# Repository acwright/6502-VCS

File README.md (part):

6502-VCS
========

An **AC6502** retro-style 8-bit computer based on the **65C02** microprocessor.

> 📖 **Guide:** [AC6502 Documentation](https://acwright.github.io/6502-DOCS/) — the user's and programmer's guide for the whole family.
> See [VCS's page in the family appendix](https://acwright.github.io/6502-DOCS/family/vcs).

---

**Building one? Every part you need, with supplier numbers and known issues, is in [BOM.md](BOM.md).**

## Table of Contents

- [Overview](#overview)
- [Architecture](#architecture)
- [Systems](#systems)
- [Software](#software)
- [Hardware](#hardware)
  - [Main Board](#main-board)
  - [Input Board](#input-board)
  - [Output Board](#output-board)
  - [ROM Cart](#rom-cart)
  - [Flash Cart](#flash-cart)
  - [Flash Helper](#flash-helper)
- [Which revision to make](#which-revision-to-make)
- [Works with the stock BIOS](#works-with-the-stock-bios)
- [Firmware](#firmware)
  - [IB Controller](#ib-controller)
- [CAD](#cad)
- [Production](#production)
- [Schematics](#schematics)
- [Shared lines](#shared-lines)
- [Extra pins: `EXP0`–`EXP3` and `HRDB`](#extra-pins-exp0exp3-and-hrdb)
- [Jumpers](#jumpers)
- [Off-board headers](#off-board-headers)
- [Libraries](#libraries)
- [Bill of Materials](#bill-of-materials)
- [License](#license)

---

## Overview

The AC6502 ecosystem is a family of open-source, 65C02-based computers sharing a common architecture, memory map, and [BIOS](https://github.com/acwright/6502-BIOS). Each computer in the family is purpose-built for a different use case but runs the same software and firmware.

The **VCS** is a cartridge-based retro gaming console. It features a real 65C02 CPU, swappable ROM cartridges, VGA video output via [Pico9918](https://github.com/visrealm/pico9918), SID audio via ARMSID, and support for PS/2 keyboards, matrix keyboards, and Atari 2600-compatible joysticks.

## Architecture

All AC6502 computers share:

- **CPU**: 65C02 (or accurate emulation)
- **Memory**: 32KB RAM + 32KB ROM, with optional banked RAM expansion
- **Memory Map**: Standardized across the ecosystem — zero page, stack, I/O space ($8000–$9FFF), system ROM, and interrupt vectors at $FFFA–$FFFF
- **Bus**: 16-bit address bus, 8-bit bidirectional data bus, standard 65C02 control signals (RW, PHI2, RESET, IRQ, NMI, RDY, SYNC)
- **BIOS**: A common [BIOS](https://github.com/acwright/6502-BIOS) provides the kernel, monitor, and BASIC interpreter across all systems

## Systems

| Project | Description |
|---------|-------------|
| [6502-ACE](https://github.com/acwright/6502-ACE) | All-in-one Computer Experience — A single board computer |
| [6502-COB](https://github.com/acwright/6502-COB) | Computer On a Backplane — Modular desktop computer with expandable card slots |
| [6502-DEV](https://github.com/acwright/6502-DEV) | Development Environment Vehicle — Emulation-based dev system |
| [6502-KIM](https://github.com/acwright/6502-KIM) | Keypad Input Monitor - KIM-1 inspired minimal computer |
| [6502-VCS](https://github.com/acwright/6502-VCS) | Video Computer System — Cartridge-based retro gaming console (YOU ARE HERE) |

## Software

| Project | Description |
|---------|-------------|
| [6502-BIOS](https://github.com/acwright/6502-BIOS) | The shared BIOS (kernel, monitor, BASIC) for all AC6502 computers |
| [6502-EMULATOR](https://github.com/acwright/6502-EMULATOR) | Emulator for the whole family — desktop app, browser build, and a command line for scripted runs |
| [6502-PRG](https://github.com/acwright/6502-PRG) | Template project for writing assembly language programs |
| [6502-CRT](https://github.com/acwright/6502-CRT) | Template project for writing assembly language cartridges |
| [6502-ASM](https://github.com/acwright/6502-ASM) | Assembly language example programs and demos |
| [6502-BAS](https://github.com/acwright/6502-BAS) | BASIC program listings |
| [6502-WOZMON](https://github.com/acwright/6502-WOZMON) | Wozmon as a standalone ROM |
| [6502-NOP](https://github.com/acwright/6502-NOP) | An all-NOP ROM, for probing a board during bring-up |
| [6502-DOCS](https://github.com/acwright/6502-DOCS) | The documentation site — the guide, the printable reference cards, branding and label artwork |
| [cffs](https://github.com/acwright/cffs) | Builds CompactFlash disk images for the BIOS filesystem |
| [bastok](https://github.com/acwright/bastok) | Tokenizes BASIC listings into `.prg` images, and back |
| [bin2woz](https://github.com/acwright/bin2woz) | Converts a binary into a Wozmon serial upload |

## Hardware

This repository contains KiCad 7.0+ PCB designs for the boards that make up the VCS system.

### Main Board
`Hardware/Main Board/`

The core board containing the 65C02 CPU, 32KB SRAM, 32KB EEPROM, clock, and reset circuitry. Runs at 1 MHz and provides the bus connection for the Input and Output boards.

### Input Board
`Hardware/Input Board/`

Unified input board supporting a matrix keyboard, PS/2 keyboard, and Atari 2600-compatible joysticks. Uses a 65C22 VIA and an ATmega1284 microcontroller as the keyboard encoder controller.

The joysticks share the VIA ports with the keyboard encoder rather than having connectors of their own: they come in on the `J1` PORT B and `J2` PORT A box headers, with `JOY(1)` reading PORT B and `JOY(2)` reading PORT A. See [Joystick Interface](./Firmware/IB%20Controller/README.md#joystick-interface) for the wiring options and the bitmask the BIOS returns.

### Output Board
`Hardware/Output Board/`

Combined VGA video output (via Raspberry Pi Pico running [Pico9918](https://github.com/visrealm/pico9918)) and SID audio output (via ARMSID). Provides TMS9918A-compatible graphics modes at 640×480 VGA and 3-voice SID synthesis.

### ROM Cart
`Hardware/ROM Cart/`

Swappable ROM cartridge for the VCS system. Rev 1.0 came in two versions, one for each ROM chip:

- **Rev 1.0a** — Uses the **28C256** 32KB EEPROM (electrically erasable, no UV eraser required).
- **Rev 1.0b** — Uses the **27C256** 32KB EPROM (UV-erasable).

**Rev 1.1** (drawn, not yet made) takes either chip. Two solder jumpers, JP1 and JP2, ship set for the 28C256
(`28C`); cut and re-bridge both to `27C` for a 27C256. It also has an option for tinkerers, not fitted:
J2, `ROM BANK`, picks the chip's upper 16K (`HI`, as made) or its lower 16K (`LO`), so one chip can hold two
programs. See *Jumpers* below and the build notes in `BOM.md`.

### Flash Cart
`Hardware/Flash Cart/`

Banked flash cartridge, and the successor to the fixed 16K ROM Cart. One all-SMD board covers 128KB to 1MB,
depending on which parts are populated, and the flash is programmed in circuit through the card edge, either by
the Flash Helper (an Arduino Mega 2560 shield with one connector on it) or by the 6502 itself.

- `$C000–$DFFF` is a switchable 8K window, selected by a write-only bank register at `$E000–$FFFF`.
- `$E000–$FFFF` is fixed to the last 8K of the primary flash, so the vectors and the bank-switching code can
  never be mapped out.
- Existing 16K cart images run unmodified.
- **Tested in the 512KB and 1MB builds** (2026-11-09): programmed through the Flash Helper, and run on an ACE,
  banking into both chips and saving across a power cycle. The 128KB and 256KB builds (SST39SF010A, SST39SF020A)
  use the same board but haven't been built yet.
- Its 0.5 mm TSOP parts make it the hardest board in the family to build by hand: having JLCPCB assemble it is the
  preferred way to get one. See the build notes in [BOM.md](BOM.md#build-notes).

See [DESIGN.md](./Hardware/Flash%20Cart/Rev%201.0/DESIGN.md) for the memory map, the logic, the programming
sequences and the build variants.

### Flash Helper
`Hardware/Flash Helper/`

The programmer for the Flash Cart: an Arduino Mega 2560 R3 shield with a cartridge slot on it, and
nothing else. It pretends to be the 65C02 on the far side of the card edge, so a cart is programmed
in circuit with no chip ever removed — which matters, because the flash is a soldered-down TSOP part.

- Two parts: the Arduino, and the same TE card edge connector the Main Board fits as J9.
- Thirty-seven of the forty card edge pins: `A0–A15`, `D0–D7`, `RWB`, `PHI2`, `RESB`, `IRQB`, `NMIB`,
  `VCC` and `GND`.
- `EXP0` and `EXP1` are deliberately **not** connected. Cartridges tie them to GND to disable the
  system ROM, so driving them would be a short.
- Host side is `6502-flash`, a Node CLI. See [DESIGN.md](./Hardware/Flash%20Cart/Rev%201.0/DESIGN.md).

**As a card tester.** Every card in the AC6502 family — the [COB](https://github.com/acwright/6502-COB)
cards, the [KIM](https://github.com/acwright/6502-KIM) Keypad Card and both VCS carts — carries the same
`6502 Card Edge` fingers and drops into this socket. `IRQB` and `NMIB` are wired for that reason rather
than for programming: the GPIO, LCD, Serial and Serial Card Pro cards all assert `IRQB`, and a tester
that could not see it would miss most of what they do. That firmware is a separate build and does not
exist yet.

<!-- Which revision to make: generated by Tools/revision-audit/register.py from Tools/data/orders.json. Edit that file, not this section. -->
## Which revision to make

**Make the newest revision of a board, and check its label first.** The table below gives each board's newest revision. A newer revision fixes what was found on the older ones. Every revision, old and new, is in [REVISIONS.md](REVISIONS.md), with what changed in each.

Each revision carries one of three labels:

- **Tested:** This revision was built and tested.
- **Proven design:** Not built at this revision, but its circuit is proven. Either it is a tested revision's circuit, or each change copies a circuit built and tested on another board or on the bench, or is a textbook circuit that leaves everything the tested revision does as it was. Any other change is silkscreen text, part values, mounting holes, outline clean-up, parts moved a fraction of a millimetre onto their grid, capacitor pitch, socket outlines, a footprint swap with the same holes, a solder jumper's default, the solder mask or paste at a card edge, or tracks rerouted or pours refilled with DRC and the netlist check passing. A builder can treat it as tested.
- **Untested:** The circuit, the power path or the layout changed in a way that only a built board proves, or the board has never been built at all.

[BOM.md](BOM.md) has the parts for every revision, and its known issues.

| Board | Newest revision | Label | Why |
|---|---|---|---|
| Flash Cart | 1.1 | **Proven design** | The bare card edge and the shell's holes at their nominal places. |
| Flash Helper | 1.1 | **Proven design** | J1's reference resized and the logo moved; silkscreen only. |
| Input Board | 1.1 | **Proven design** | Silkscreen text, and 10k pull-ups on the PS/2 lines, a textbook circuit not yet tried on these lines. |
| Main Board | 1.1 | **Proven design** | 10k pull-ups, small part moves and tracks rerouted, a 74HCT00 at U5, and the RAM's output enable from inverted `RWB`, tested on an ACE. The jumpers are gone, and `HRDB` is wired as it is on the tested Rev 1.0 with them fitted. |
| Output Board | 1.1 | **Proven design** | `A1` wired to the pico9918's `MODE1`, so the VCS can run BIOS 2.x, as the tested ACE is wired; a second RCA jack beside J2, on the same signal, as on the ACE; ordinary sockets in place of ZIF, on the ACE's footprints; silkscreen text, the `VDD` header removed, JP1 ships open, and JP2 and JP3 removed and wired as Rev 1.0 ships them. |
| ROM Cart | 1.1 | **Proven design** | Either ROM chip through two solder jumpers, each setting a tested board's wiring; a ROM bank option, not fitted, whose pull-up reads the half Rev 1.0 reads; capacitor pitch; the bare card edge and the shell's holes at their nominal places. |
<!-- End of which revision to make -->

<!-- Stock BIOS: generated by Tools/bios/gen.py from Tools/data/bios.json. Edit that file, not this section. -->
## Works with the stock BIOS

Whether each board works with the stock BIOS, and what it takes if not. The stock BIOS for the VCS is **BIOS 1.x**, from the `v1.x` branch of [6502-BIOS](https://github.com/acwright/6502-BIOS). The ACE runs BIOS 2.x, for a 6502-PICOVDP. A VCS can also run BIOS 2.x with an Output Board 1.1, or an Output Board 1.0 with the optional wire in its build note, carrying a PICO9918 PRO running 6502-PICOVDP, set up as the [ACE's video card](https://github.com/acwright/6502-ACE#video-card) is. Today's VCSs, built with an Output Board 1.0, stay on BIOS 1.x. The BIOS looks for each card in its own 1 KB window at boot, and uses only what it finds.

- **Compatible:** the BIOS finds the board and uses it, built from its parts list with the jumpers the [Jumpers](#jumpers) table gives. A card counts only on the window the BIOS expects; on another window it's the builder's experiment.
- **After a step:** it works once the builder does what the entry names, beyond the parts list and the jumpers.
- **Not used by the BIOS:** safe beside it, but your own software drives it.
- **Nothing to support:** the board has no registers for the BIOS to find, such as a backplane, a helper behind a card, or a cartridge's programmer.

| Board | Rev | Stock BIOS | Why | Source |
|---|---|---|---|---|
| Flash Cart | 1.0, 1.1 | **Compatible** | A cartridge: with one in, `HRDB` gives it `$C000`–`$FFFF` and the reset vector, and its program calls the BIOS's Kernal, which stays at `$A000`–`$B7FF`. | README [Extra pins](#extra-pins-exp0exp3-and-hrdb); bench, 2026-11-09 |
| Flash Helper | 1.0, 1.1 | **Nothing to support** | A programmer for the Flash Cart, on an Arduino Mega: it's never in a machine. | Schematic |
| Input Board | 1.0, 1.1 | **Compatible** | Its 65C22 VIA answers in IO 6 (`$9400`), where the BIOS looks for the keyboard and joystick VIA. | BIOS 1.x `Kernal.asm` `ProbeGPIO` |
| Main Board | 1.0, 1.1 | **Compatible** | The 65C02, RAM and the ROM that holds the BIOS. Rev 1.0 needs its power, clock and `HRDB` jumpers set, as the [Jumpers](#jumpers) table says; Rev 1.1 has them wired. | Schematic; README [Jumpers](#jumpers) |
| Output Board | 1.0 | **After a step** | Cut JP1, as its build note says: bridged, as made, it lets the pico9918 hold `IRQB` high, so the Input Board's interrupts don't reach the 65C02. Then the BIOS finds the SID in IO 7 (`$9800`) and the pico9918, a TMS9918A to BIOS 1.x, in IO 8 (`$9C00`). For BIOS 2.x, the build note also has an optional wire from `A1` to the pico9918's `MODE1`. | BIOS 1.x `Kernal.asm` `ProbeSID`, `ProbeVideo`; BOM.md build notes |
| Output Board | 1.1 | **Compatible** | The BIOS finds the SID in IO 7 (`$9800`) and the pico9918, a TMS9918A to BIOS 1.x, in IO 8 (`$9C00`). JP1 ships open. Rev 1.1 also lets a VCS run BIOS 2.x: `A1` reaches the pico9918's `MODE1`, so a PICO9918 PRO running 6502-PICOVDP answers on both its port pairs, as on the ACE. | BIOS 1.x `Kernal.asm` `ProbeSID`, `ProbeVideo`; BIOS 2.x `Kernal.asm` `ProbeVideo` |
| ROM Cart | 1.0a, 1.0b, 1.1 | **Compatible** | A cartridge: with one in, `HRDB` gives it `$C000`–`$FFFF` and the reset vector, and its program calls the BIOS's Kernal, which stays at `$A000`–`$B7FF`. | README [Extra pins](#extra-pins-exp0exp3-and-hrdb) |

<!-- End of stock BIOS -->

## Firmware

This repository contains [PlatformIO](https://platformio.org/)-based firmware for the Input Board.

### IB Controller
`Firmware/IB Controller/`

Firmware for the ATmega1284 on the Input Board. Provides:

- Matrix keyboard scanning and encoding
- PS/2 keyboard interface
- Atari 2600-compatible joystick input
- Parallel I/O to the AC6502 bus via 65C22 VIA

See [Firmware/IB Controller/README.md](./Firmware/IB%20Controller/README.md) for setup and usage instructions.

## CAD
`CAD/`

3D-printable enclosure parts and laser-cut top panels for the VCS system.

**Board images** are in `CAD/Images/<Board>/Rev X/`: `Front.png` and `Back.png` on white, and `Front Transparent.png` and `Back Transparent.png` with no background. Every image is a 3D render at the same size, with the black solder mask and white silkscreen the boards are made with. Bare-board photos may differ, because the renders show parts fitted.

**Top panels are versioned by board revision**, like `Hardware/`: `CAD/Tops/<Board>/Rev X/`. Each revision has its own complete folder, even when two revisions share the same files. `Bases/` holds the parts for a whole computer, not for one board, so it isn't versioned.

The **[plate mounting drawing](CAD/Bases/Plate%20Mounting%20Drawing.png)** ([SVG](CAD/Bases/Plate%20Mounting%20Drawing.svg)) shows where the Output Board, the Main Board and the Input Board mount on the base plate, with every hole's position and the hardware the build needs. The plate is a stack of three 3 mm acrylic layers.

## Production
`Production/`

[REVISIONS.md](REVISIONS.md) lists every board revision: whether it was made, its JLCPCB order, the commit it was made from, and what fits it.

JLCPCB-ready Gerber files and BOM/CPL for PCB fabrication and assembly.

## Schematics
`Schematics/`

PDF schematics for each board.

## Shared lines

Five lines of the 6502 bus are shared by every board on it: `RESB`, `IRQB`, `NMIB`, `RDY` and `BE`. A board may pull one of these lines low, and nothing drives one high. Each line is held high by one 10kΩ pull-up resistor to VCC, on the board with the CPU: the ACE Board, the KIM Board, the VCS Main Board, the COB CPU Card or CPU Card Pro, or the DEV Board. No other board has one. Two pull-ups on the same line would sit in parallel and lower its resistance, so a card that adds its own pull-up changes the machine for every other board. The VIAs and PIAs in the BOMs, the W65C22N and W65C21N, have open-drain interrupt outputs for this reason.

**Interrupt outputs.** Whatever drives `IRQB` or `NMIB` may only pull it low. Every board is drawn for the parts in its BOM and works as shipped, with no jumper to cut or bridge:

- **A part whose interrupt output is open-drain** (the W65C22N, W65C21N, R6551AP, DS1511Y, DS1501 and TMS9918A) drives the line directly, or through a diode with a solder jumper across it that ships bridged. The diode is fitted either way. To use a part that drives its interrupt high as well as low instead, such as a W65C22S or a replacement of your own, cut the jumper: the diode then lets the part only pull the line low. A board with no diode in the line can't take such a part.
- **A part that drives its interrupt high as well as low** (the pico9918, the VERA module, and a microcontroller such as the ATmega1284 or a Raspberry Pi Pico) reaches the line through a diode, a BAT85 or a 1N914, with its cathode toward the part. Where a solder jumper sits across that diode, it ships open. The diode is then the only path to the line, so fit it, and never bridge the jumper, because the part would then hold the line high against every other interrupt source.
- **A microcontroller wired to the line directly,** as on the ACE Board, the Mega Helper and the Flash Helper, drives it open-drain in its firmware: it sets the pin low or leaves it as an input, and never drives it high.

The *Jumpers* section below gives each board's interrupt jumper.

The same holds where a board has its own reset circuit. A reset switch, its timer and the transistor that pulls `RESB` low can be on any board, such as the COB Backplane Pro or the Clock Card, but the `RESB` pull-up is only ever on the board with the CPU. Each of those boards draws its pull-ups together, in one group on its schematic.

The DEV Board is the exception on `RESB`. It stands in for a Main Board, so it owns reset: its Reset button goes to the Teensy, and the Teensy drives `RESB` onto the bus through U3, a level shifter that only sends signals out, as it drives `PHI2`. U3 holds `RESB` high or low, so the DEV Board has no `RESB` pull-up, and nothing else on its bus may pull `RESB` low. Connect a DEV only to a passive backplane, never to the COB Backplane Pro, whose reset circuit would pull against U3, and don't fit a card that pulls `RESB` low, such as the COB RTC Card.

`SOB` is a CPU pin that isn't on the bus. It is tied to VCC, directly or through a 10kΩ resistor.

A few chips have a pull-up of their own inside the chip, such as an ATmega's reset pin. Where such a pin is wired to `RESB`, its pull-up of 30–60kΩ sits in parallel with the 10kΩ one. That's harmless, because whatever pulls `RESB` low can sink the extra current many times over.

A revision that doesn't follow this yet says so in its known issues in [BOM.md](BOM.md), with what to fit or remove.

## Extra pins: `EXP0`–`EXP3` and `HRDB`

`EXP` stands for "extra pin". Four pins of the 6502 bus are left for a builder's own use: pin 4 is `EXP1`, pin 6 is `EXP0`, pin 19 is `EXP3` and pin 21 is `EXP2`.

Pins 4 and 6 have a second job. A cartridge ties both of them to GND. That pulls `HRDB` ("High ROM disable bar", active low) low on the board with the ROM, which takes `$C000–$FFFF` away from the ROM so that the cartridge answers there instead. So in a build that uses cartridges, pins 4 and 6 are reserved for `HRDB`, and nothing else may drive them. They are free as `EXP1` and `EXP0` only in a build that never uses cartridges. `EXP2` and `EXP3` are always free.

How the boards treat pins 4 and 6:

- **The ACE Board and the KIM Board** join them to their ROM's `HRDB` input, and their silk says `HRDB`. The VCS Main Board joins them the same way from Rev 1.1.
- **The COB Memory Card** joins them to its `HRDB` only through jumpers: fit two shunts on J2, or bridge JP1 and JP2, in a COB that takes cartridges. It is the only board with these jumpers, because the COB is the experimenter's build. The VCS Main Board Rev 1.0 had them too (J5, or JP3 and JP4); fit them, because the VCS always takes cartridges.
- **A cartridge** (the ROM Cart, the Flash Cart, the KIM Keypad Card) ties them to GND.
- **A board that only carries the bus through**, such as a backplane or a helper, calls them `EXP1` and `EXP0`, as its silk does, and a note on its schematic says what they carry.

<!-- Jumpers: generated by Tools/jumpers/gen.py from Tools/data/jumpers.json. Edit that file, not this section. -->
## Jumpers

Some boards have solder jumpers, and pin headers that take a shunt. The tables below give every one: what it's for, how the board is shipped, and what to do with it. The **Needed** column marks the ones that matter:

- **To run**: the board doesn't work until this is set. Set it before the first power-up.
- **For serial**, **For interrupts**, **For cartridges**: the board runs without it, but that feature doesn't.
- Blank: leave it as shipped unless you want what it offers.

Where a header needs a shunt, the board's BOM lists it.

**Input Board**

| Rev | Jumper | What it's for | As shipped | What to do | Needed |
|---|---|---|---|---|---|
| 1.0, 1.1 | J6 | I/O window: one shunt picks the 1 KB window the board answers in. | No shunt. | Fit the shunt beside `$9400`: IO 6, where the BIOS looks for the Input Board. | To run |
| 1.0, 1.1 | JP1 | Across D1, the diode in the W65C22N's interrupt line. | Bridged. | Leave it. The W65C22N's interrupt output is open-drain: it only pulls the line low, so the board works as shipped and D1 isn't needed. To fit a part that drives its interrupt high as well as low, such as a W65C22S, cut JP1 so the interrupt goes through D1. |  |

**Main Board**

| Rev | Jumper | What it's for | As shipped | What to do | Needed |
|---|---|---|---|---|---|
| 1.0 | J5, JP3, JP4 | `HRDB EN`: joins the bus's `EXP1` and `EXP0` to the ROM's High ROM disable. | Open, no shunts. | Fit two shunts on J5, or bridge JP3 and JP4: without them a cartridge can't take `$C000–$FFFF`, and the VCS always takes cartridges. Rev 1.1 wires them. | For cartridges |
| 1.0 | J8 | `EXP EN`: shunts here join CPU signals (`VPB`, `MLB`, `SOB`, `PHI1O`, `PHI2O`) to the bus's extra pins. | No shunts. | Leave it empty: the VCS takes cartridges, which ground `EXP0` and `EXP1`. Rev 1.1 has no J8. |  |
| 1.0 | JP1, J2 | `ROM WE`: joins the ROM's `/WE` to the write strobe, so a program can write the EEPROM in circuit. | Open, no shunt. | Leave it open: R1 holds `/WE` high. Rev 1.1 ties `/WE` to VCC. |  |
| 1.0 | JP2, J1 | Power: JP2 is across J1 (`PWR_SW`), the header for a power switch. | Open. | Bridge JP2, or wire a switch to J1. Until one is done the board has no power. Rev 1.1 has neither. | To run |
| 1.0 | JP5, J7 | Original 6502: grounds pin 1, which is `VSS` on an NMOS 6502 and `VPB` on a 65C02. | Open, no shunt. | Leave both open for a 65C02. Rev 1.1 has neither. |  |
| 1.0 | JP6, J6 | Clock: JP6 is across J6 (`CLOCK_ENBL_SW`), the header for a switch that stops the clock. | Open. | Bridge JP6, or wire a switch to J6. Until one is done there is no clock on `PHI2`. Rev 1.1 has neither. | To run |

**Output Board**

| Rev | Jumper | What it's for | As shipped | What to do | Needed |
|---|---|---|---|---|---|
| 1.0, 1.1 | J6 | Interrupt: one shunt sends the board's interrupt to `IRQB` or `NMIB`. | No shunt. | Fit the shunt on `IRQB`, which the BIOS expects. With no shunt the interrupt reaches neither. | For interrupts |
| 1.0, 1.1 | J7 | I/O windows: two shunts pick the windows for the sound chip and the video chip. | No shunts. | Fit one shunt beside `$9800` (IO 7) for the sound chip and one beside `$9C00` (IO 8) for the video chip, where the BIOS looks for them. | To run |
| 1.0 | JP1 | Across D1, the diode in the pico9918's interrupt line. | Bridged. | Cut JP1. The pico9918 drives its interrupt high as well as low, and only D1 stops it holding `IRQB` high against every other interrupt source. Rev 1.1 ships it open. | For interrupts |
| 1.0 | JP3, JP2 | JP3 feeds `PHI2` to an enable of U3, a 74HC138, so the board is selected only while `PHI2` is high. JP2 would tie that enable high instead. | JP3 bridged, JP2 open. | Leave them. With `PHI2` on the decoder's enable, the card's read and write strobes last only while `PHI2` is high, when the 6502's address and data are valid, as the chips need. Tied high, the strobes would run through the whole cycle and glitch while the address settles. Rev 1.1 has no jumpers here: `PHI2` goes straight to the enable. |  |
| 1.1 | JP1 | Across D1, the diode in the pico9918's interrupt line. | Open. | Leave it open. The pico9918 drives its interrupt high as well as low, and D1 lets it only pull `IRQB` low. Bridged, JP1 would let it hold the line high against every other interrupt source. Never bridge it. Fit D1, which the BOM lists: with the jumper open it is the only path to the line, so without it the board never interrupts. |  |

**ROM Cart**

| Rev | Jumper | What it's for | As shipped | What to do | Needed |
|---|---|---|---|---|---|
| 1.1 | J2 | ROM bank: which 16K half of the ROM chip the cart reads. An option for tinkerers, not fitted. | Not fitted. R1 holds the ROM on its upper 16K (`HI`). | Nothing, for a one-program cart. To read the lower 16K, fit a 3-pin header and a shunt on `LO`; on `HI`, or with no shunt, it reads the upper 16K. Keep R1 fitted either way. |  |
| 1.1 | JP1, JP2 | ROM chip: two three-pad solder jumpers set U1 for an AT28C256 EEPROM (`28C`) or an AT27C256 EPROM (`27C`). JP1 puts `A14` or VPP's `VCC` on pin 1; JP2 puts `VCC`, holding the EEPROM's `/WE` high, or `A14` on pin 27. | Bridged 1–2 on both, `28C`, for the AT28C256. | Leave both on `28C` for the AT28C256 the parts list orders. For an AT27C256, cut the bridge between pads 1 and 2 on both, check with a meter that they no longer connect, and bridge pads 2 and 3 (`27C`) on both. Never fit an AT28C256 with the jumpers on `27C`: its `/WE` would be on `A14`, so a write to the cart's addresses could overwrite it. |  |

<!-- End of jumpers -->

<!-- Off-board headers: generated by Tools/offboard/gen.py from Tools/offboard/offboard.json, Tools/data/offboard.json and the PCB files. Edit those, not this section. -->
## Off-board headers

Some boards have small headers, such as `RESET SW`, `CLOCK ENBL SW`, `POWER LED` and `VCC`, that a standard build leaves empty. They are for a machine built into a full enclosure, which AC6502 doesn't offer today. In such a build, the parts a person handles are mounted on the case and wired to the board through these headers: the power jack, the switches, the LEDs and the keyboard. The matching parts on the board are then left off. For example, an ACE Board can sit inside a case with its power jack, power switch and key switches left off, and a Keyboard Helper as its keyboard.

To build a board for a case:

1. Fit the header, and wire the part on the case to it. The table says what goes on each pin.
2. Leave off the parts on the board that the table names. A button on the case can work beside the board's own button, but some parts, such as an LED that shares the board's resistor, can't share.
3. Set any jumper the table mentions. The [Jumpers](#jumpers) section has the rest.

The connector follows the kind of build. A single-board machine, the ACE Board or the KIM Board, uses plain 2.54 mm pin headers, which are simpler and cheaper. A board in a multi-board machine, every COB board and the separate boards of the VCS, the DEV and the KIM, uses JST XH, the family's standard for these headers.

The table lists every off-board header on each board's newest revision, read from the board's PCB file.

| Board | Rev | Header | Label | Connector | What it's for | Leave off |
|---|---|---|---|---|---|---|
| Main Board | 1.1 | J4 | `RESET SW` | JST XH, 2 pins | A reset button on the case. The header is wired across SW1, the board's own reset button. | SW1, if the case covers it. Both buttons reset the machine if it stays. |

<!-- End of off-board headers -->

## Libraries
`Libraries/`

Shared KiCad symbol and footprint libraries used across all AC6502 hardware projects, with their 3D models in `Models/`. A part is named for what it is and its shape, such as `RJ45 Jack LED` or `CR2032 Holder`, never for a manufacturer's part number, so a replacement part with the same footprint fits without renaming anything. The part numbers to buy are in [BOM.md](BOM.md). Every AC6502 repository carries the same copy of each part.

## Bill of Materials

Every part for every board, by revision, is in **[BOM.md](BOM.md)**, with supplier numbers, known issues, build notes and files to upload to Digi-Key and Mouser. What changed in each revision, and what is known about each one, is in **[REVISIONS.md](REVISIONS.md)**.

## License

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
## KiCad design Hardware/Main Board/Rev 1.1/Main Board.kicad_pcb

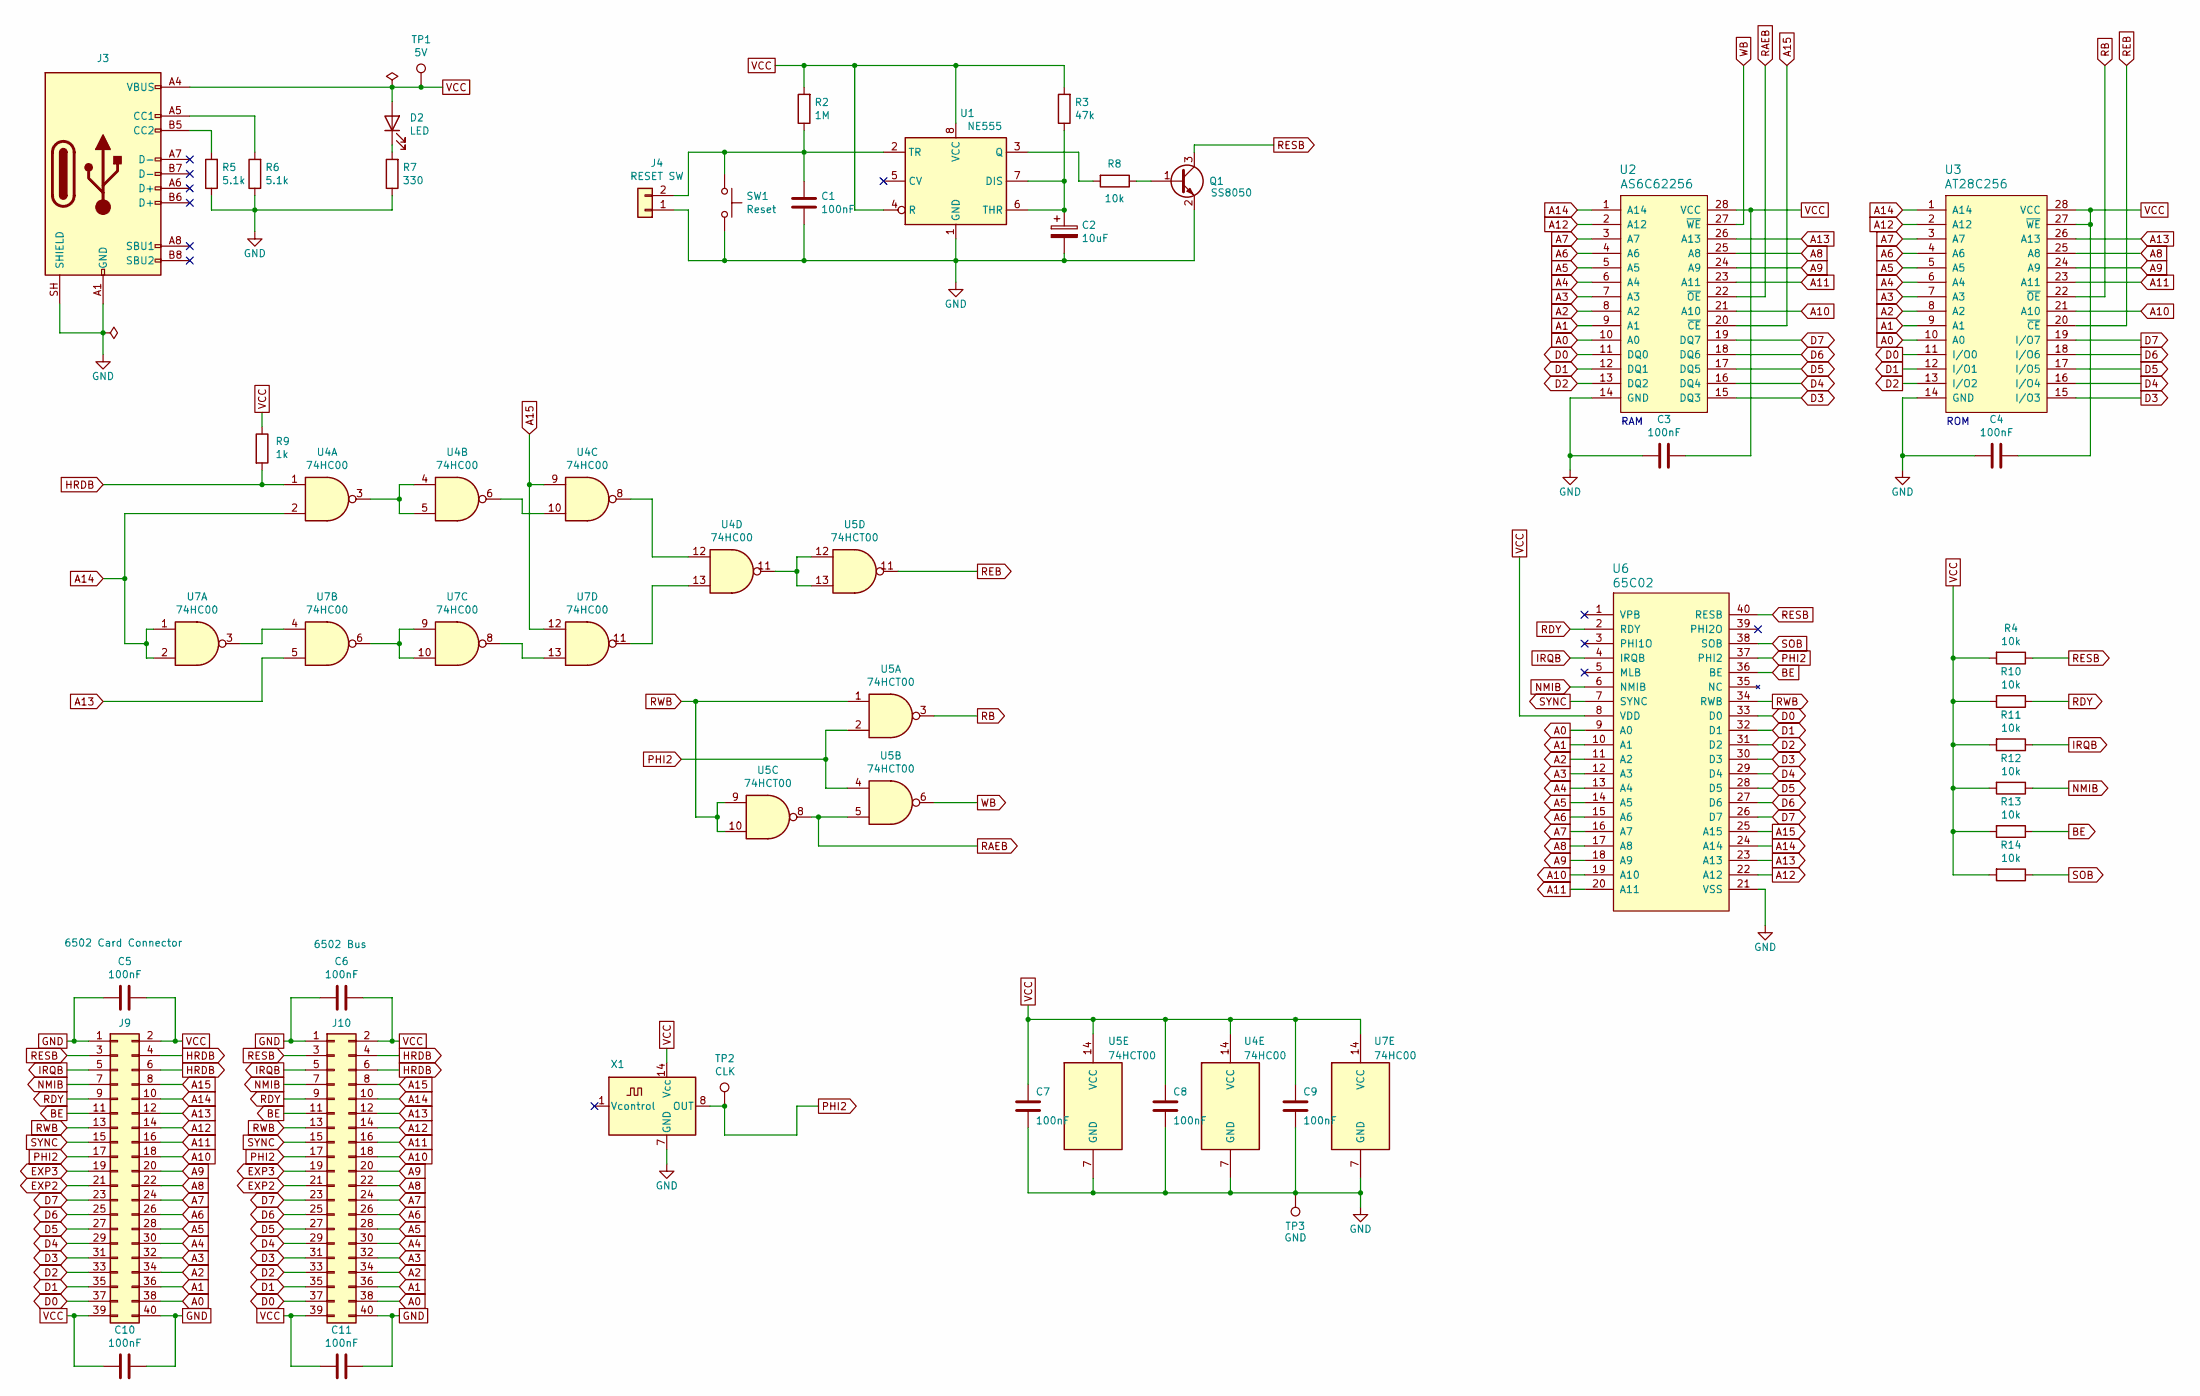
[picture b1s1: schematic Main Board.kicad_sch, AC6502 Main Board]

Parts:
C1, C3, C4, C5, C6, C7, C8, C9, C10, C11: 100nF; C_0805_2012Metric; LCSC C49678
C2: 10uF; C_1206_3216Metric; LCSC C7171
D2: LED; LED_0805_2012Metric; LCSC C2297
J3: USB_C_Receptacle_USB2.0; USB_C_Receptacle_HRO_TYPE-C-31-M-12; LCSC C2988369
J4: RESET SW; JST_XH_B2B-XH-A_1x02_P2.50mm_Vertical; Digikey 455-B2B-XH-A-ND
J9: 6502 Card Connector; 6502 Card Slot; Mouser 571-5-5530843-4
J10: 6502 Bus; 6502 Bus Connector; Digikey 732-5401-ND
Q1: SS8050; SOT-23; LCSC C2150
R2: 1M; R_0805_2012Metric; LCSC C17514
R3: 47k; R_0805_2012Metric; LCSC C17713
R4, R8, R10, R11, R12, R13, R14: 10k; R_0805_2012Metric; LCSC C17414
R5, R6: 5.1k; R_0805_2012Metric; LCSC C27834
R7: 330; R_0805_2012Metric; LCSC C17630
R9: 1k; R_0805_2012Metric; LCSC C17513
SW1: Reset; Tact Switch SMD 5.1mm; LCSC C318884
TP1: 5V; TestPoint_Pad_1.0x1.0mm
TP2: CLK; TestPoint_Pad_1.0x1.0mm
TP3: GND; TestPoint_Pad_1.0x1.0mm
U1: NE555; SOIC-8_3.9x4.9mm_P1.27mm; LCSC C7593
U2: AS6C62256; DIP-28_W15.24mm_Socket_LongPads; Digikey 1450-1033-ND
U3: AT28C256; DIP_Socket-28_W11.9mm_W12.7mm_W15.24mm_W17.78mm_W18.5mm_3M_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; Digikey AT28C256-15PU-ND
U4, U7: 74HC00; SOIC-14_3.9x8.7mm_P1.27mm; LCSC C5586
U5: 74HCT00; SOIC-14_3.9x8.7mm_P1.27mm; LCSC C6764
U6: 65C02; DIP-40_W15.24mm_Socket_LongPads; Mouser 955-W65C02S6TPG-14
X1: 1 MHz; Oscillator_DIP-14; Digikey X937-ND

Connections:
A0: J9.38, J10.38, U2.10 (A0), U3.10 (A0), U6.9 (A0)
A1: J9.36, J10.36, U2.9 (A1), U3.9 (A1), U6.10 (A1)
A2: J9.34, J10.34, U2.8 (A2), U3.8 (A2), U6.11 (A2)
A3: J9.32, J10.32, U2.7 (A3), U3.7 (A3), U6.12 (A3)
A4: J9.30, J10.30, U2.6 (A4), U3.6 (A4), U6.13 (A4)
A5: J9.28, J10.28, U2.5 (A5), U3.5 (A5), U6.14 (A5)
A6: J9.26, J10.26, U2.4 (A6), U3.4 (A6), U6.15 (A6)
A7: J9.24, J10.24, U2.3 (A7), U3.3 (A7), U6.16 (A7)
A8: J9.22, J10.22, U2.25 (A8), U3.25 (A8), U6.17 (A8)
A9: J9.20, J10.20, U2.24 (A9), U3.24 (A9), U6.18 (A9)
A10: J9.18, J10.18, U2.21 (A10), U3.21 (A10), U6.19 (A10)
A11: J9.16, J10.16, U2.23 (A11), U3.23 (A11), U6.20 (A11)
A12: J9.14, J10.14, U2.2 (A12), U3.2 (A12), U6.22 (A12)
A13: J9.12, J10.12, U2.26 (A13), U3.26 (A13), U6.23 (A13), U7.5
A14: J9.10, J10.10, U2.1 (A14), U3.1 (A14), U4.2, U6.24 (A14), U7.1, U7.2
A15: J9.8, J10.8, U2.20 (~CE), U4.9, U6.25 (A15), U7.12
BE: J9.11, J10.11, R13.1, U6.36 (BE)
D0: J9.37, J10.37, U2.11 (DQ0), U3.11 (I/O0), U6.33 (D0)
D1: J9.35, J10.35, U2.12 (DQ1), U3.12 (I/O1), U6.32 (D1)
D2: J9.33, J10.33, U2.13 (DQ2), U3.13 (I/O2), U6.31 (D2)
D3: J9.31, J10.31, U2.15 (DQ3), U3.15 (I/O3), U6.30 (D3)
D4: J9.29, J10.29, U2.16 (DQ4), U3.16 (I/O4), U6.29 (D4)
D5: J9.27, J10.27, U2.17 (DQ5), U3.17 (I/O5), U6.28 (D5)
D6: J9.25, J10.25, U2.18 (DQ6), U3.18 (I/O6), U6.27 (D6)
D7: J9.23, J10.23, U2.19 (DQ7), U3.19 (I/O7), U6.26 (D7)
EXP2: J9.21, J10.21
EXP3: J9.19, J10.19
GND: C1.2, C2.2, C3.2, C4.2, C5.2, C6.2, C7.2, C8.2, C9.2, C10.1, C11.1, J3.A1 (GND), J3.A12 (GND), J3.B1 (GND), J3.B12 (GND), J3.SH (SHIELD), J4.1, J9.1, J9.40, J10.1, J10.40, Q1.2 (E), R5.1, R6.1, R7.1, SW1.2, TP3.1 (1_1), U1.1 (GND), U2.14 (GND), U3.14 (GND), U4.7 (GND), U5.7 (GND), U6.21 (VSS), U7.7 (GND), X1.7 (GND)
HRDB: J9.4, J9.6, J10.4, J10.6, R9.2, U4.1
IRQB: J9.5, J10.5, R11.1, U6.4 (IRQB)
NMIB: J9.7, J10.7, R12.1, U6.6 (NMIB)
unnamed: D2.1 (K), R7.2
unnamed: J3.A5 (CC1), R6.2
unnamed: J3.B5 (CC2), R5.2
unnamed: C1.1, J4.2, R2.1, SW1.1, U1.2 (TR)
unnamed: Q1.1 (B), R8.1
unnamed: C2.1, R3.1, U1.6 (THR), U1.7 (DIS)
unnamed: R8.2, U1.3 (Q)
unnamed: U4.3, U4.4, U4.5
unnamed: U4.6, U4.10
unnamed: U4.11, U5.12, U5.13
unnamed: U4.8, U4.12
unnamed: U4.13, U7.11
unnamed: U7.3, U7.4
unnamed: U7.6, U7.9, U7.10
unnamed: U7.8, U7.13
PHI2: J9.17, J10.17, TP2.1 (1_1), U5.2, U5.4, U6.37 (PHI2), X1.8 (OUT)
RAEB: U2.22 (~OE), U5.5, U5.8
RB: U3.22 (~OE), U5.3
RDY: J9.9, J10.9, R10.1, U6.2 (RDY)
REB: U3.20 (~CE), U5.11
RESB: J9.3, J10.3, Q1.3 (C), R4.1, U6.40 (RESB)
RWB: J9.13, J10.13, U5.1, U5.9, U5.10, U6.34 (RWB)
SOB: R14.1, U6.38 (SOB)
SYNC: J9.15, J10.15, U6.7 (SYNC)
VCC: C3.1, C4.1, C5.1, C6.1, C7.1, C8.1, C9.1, C10.2, C11.2, D2.2 (A), J3.A4 (VBUS), J3.A9 (VBUS), J3.B4 (VBUS), J3.B9 (VBUS), J9.2, J9.39, J10.2, J10.39, R2.2, R3.2, R4.2, R9.1, R10.2, R11.2, R12.2, R13.2, R14.2, TP1.1 (1_1), U1.4 (R), U1.8 (VCC), U2.28 (VCC), U3.27 (~WE), U3.28 (VCC), U4.14 (VCC), U5.14 (VCC), U6.8 (VDD), U7.14 (VCC), X1.14 (Vcc)
WB: U2.27 (~WE), U5.6

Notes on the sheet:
ROM
RAM

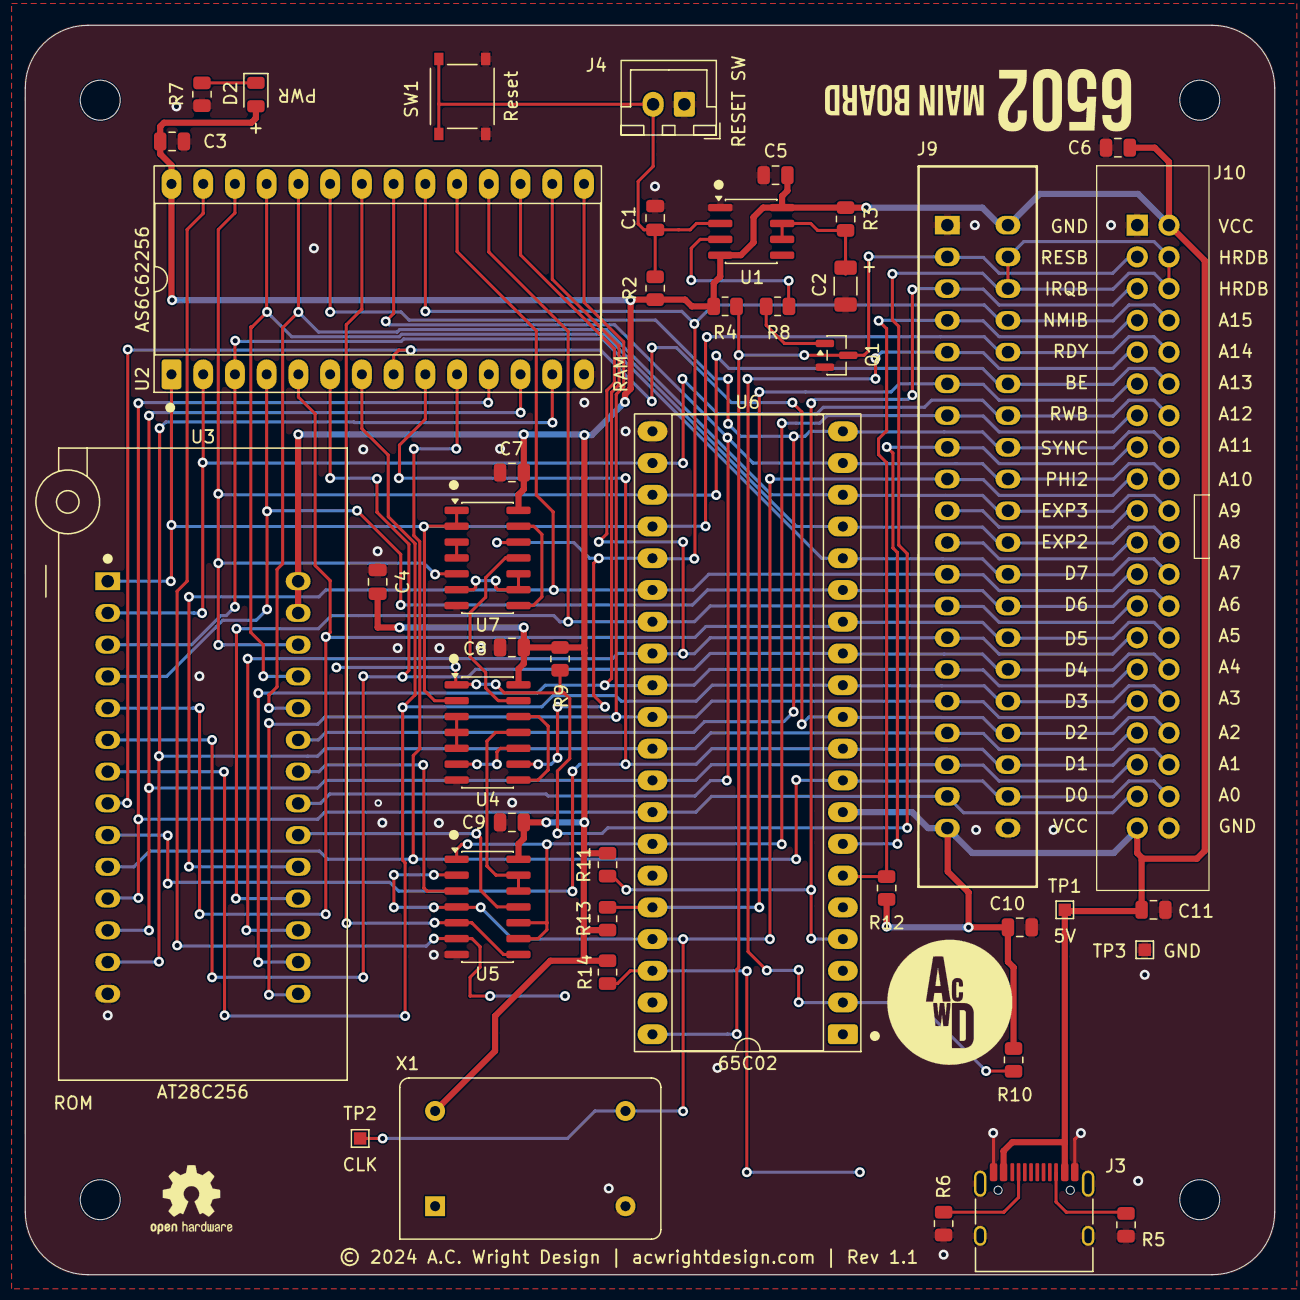
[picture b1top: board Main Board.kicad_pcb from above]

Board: 2 copper layers, 100.0 x 100.0 mm, 46 parts (0 on the bottom side), 57 nets.

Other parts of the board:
H1, H2, H3, H4: MountingHole; MountingHole_3.2mm_M3

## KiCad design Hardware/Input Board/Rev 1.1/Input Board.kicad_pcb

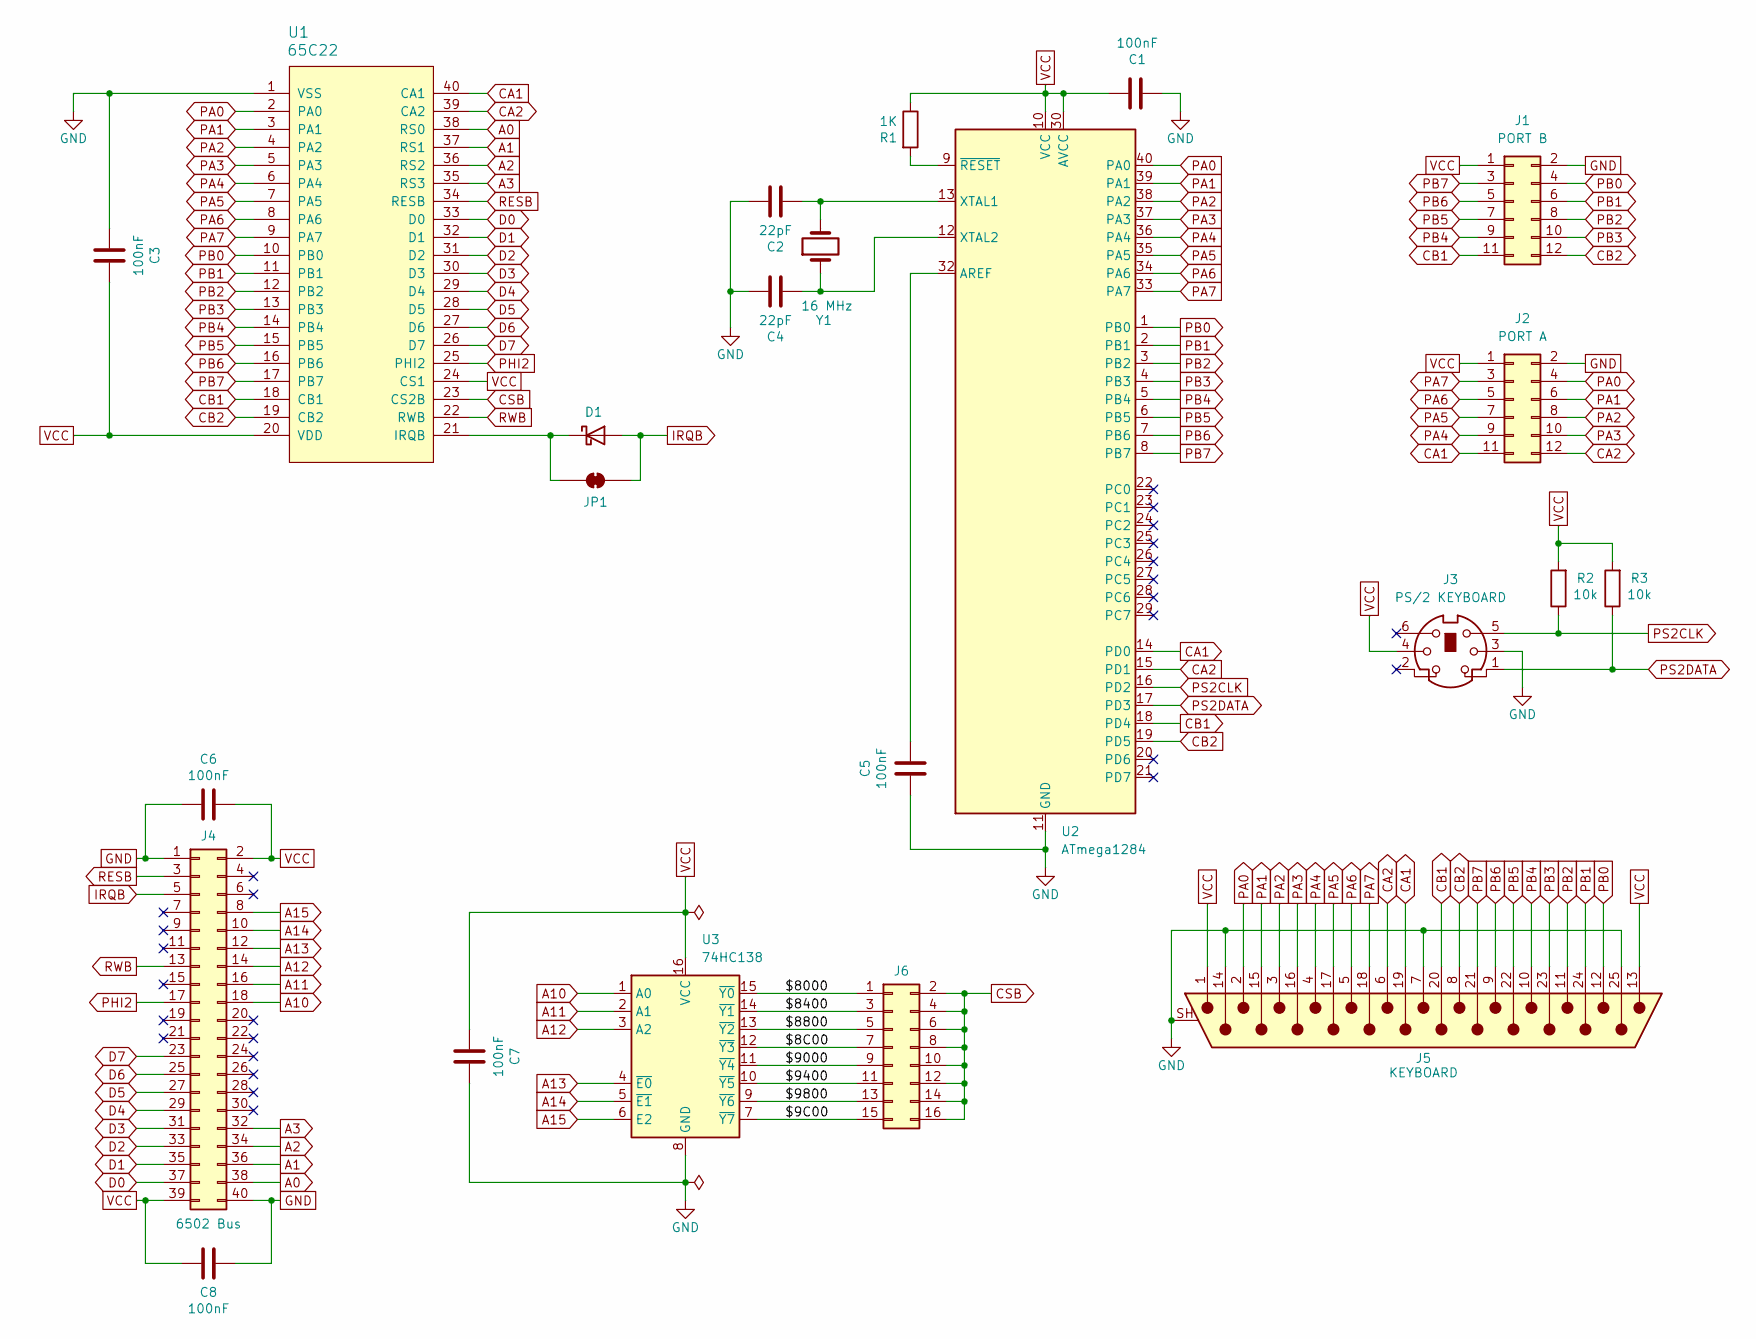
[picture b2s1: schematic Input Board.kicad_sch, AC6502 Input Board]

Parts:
C1, C3, C5, C6, C7, C8: 100nF; C_0805_2012Metric; LCSC C49678
C2, C4: 22pF; C_Disc_D5.0mm_W2.5mm_P2.50mm; Mouser 581-SR151A220JAR
D1: 1N914; D_DO-35_SOD27_P7.62mm_Horizontal; Mouser 512-1N914
J1: PORT B; 6502 GPIO Connector; Mouser 737-BHR-12-VUA
J2: PORT A; 6502 GPIO Connector; Mouser 737-BHR-12-VUA
J3: PS/2 KEYBOARD; PS2 Jack; Mouser 806-KMDGX-6S-BS
J4: 6502 Bus; 6502 Bus Connector; Mouser 710-61204021621
J5: KEYBOARD; DSUB-25_Pins_Horizontal_P2.77x2.84mm_EdgePinOffset7.70mm_Ho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; Digikey 609-1505-ND
J6: IO SELECT; PinHeader_2x08_P2.54mm_Vertical; Mouser 649-67996-140HLF
JP1: IRQ; SolderJumper-2_P1.3mm_Bridged_RoundedPad1.0x1.5mm
R1: 1K; R_0805_2012Metric; LCSC C17513
R2, R3: 10k; R_0805_2012Metric; Digikey 311-10.0KCRCT-ND
U1: 65C22; DIP-40_W15.24mm_Socket_LongPads; Mouser 955-W65C22N6TPG-14
U2: ATmega1284; DIP-40_W15.24mm_Socket_LongPads; Mouser 556-ATMEGA1284-PU
U3: 74HC138; SOIC-16_3.9x9.9mm_P1.27mm; LCSC C5602
Y1: 16 MHz; Crystal_HC49-U_Vertical; Digikey X1103-ND

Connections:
/$8C00: J6.7, U3.12 (~Y3)
/$9C00: J6.15, U3.7 (~Y7)
/$8000: J6.1, U3.15 (~Y0)
/$8400: J6.3, U3.14 (~Y1)
/$8800: J6.5, U3.13 (~Y2)
/$9000: J6.9, U3.11 (~Y4)
/$9400: J6.11, U3.10 (~Y5)
/$9800: J6.13, U3.9 (~Y6)
A0: J4.38, U1.38 (RS0)
A1: J4.36, U1.37 (RS1)
A2: J4.34, U1.36 (RS2)
A3: J4.32, U1.35 (RS3)
A10: J4.18, U3.1 (A0)
A11: J4.16, U3.2 (A1)
A12: J4.14, U3.3 (A2)
A13: J4.12, U3.4 (~E0)
A14: J4.10, U3.5 (~E1)
A15: J4.8, U3.6 (E2)
CA1: J2.11, J5.19, U1.40 (CA1), U2.14 (PD0)
CA2: J2.12, J5.6, U1.39 (CA2), U2.15 (PD1)
CB1: J1.11, J5.20, U1.18 (CB1), U2.18 (PD4)
CB2: J1.12, J5.8, U1.19 (CB2), U2.19 (PD5)
CSB: J6.2, J6.4, J6.6, J6.8, J6.10, J6.12, J6.14, J6.16, U1.23 (CS2B)
D0: J4.37, U1.33 (D0)
D1: J4.35, U1.32 (D1)
D2: J4.33, U1.31 (D2)
D3: J4.31, U1.30 (D3)
D4: J4.29, U1.29 (D4)
D5: J4.27, U1.28 (D5)
D6: J4.25, U1.27 (D6)
D7: J4.23, U1.26 (D7)
GND: C1.1, C2.2, C3.1, C4.2, C5.1, C6.2, C7.2, C8.1, J1.2, J2.2, J3.3, J4.1, J4.40, J5.7, J5.14, J5.25, J5.SH (PAD), U1.1 (VSS), U2.11 (GND), U2.31 (GND), U3.8 (GND)
IRQB: D1.2 (A), J4.5, JP1.2 (B)
unnamed: D1.1 (K), JP1.1 (A), U1.21 (IRQB)
unnamed: C5.2, U2.32 (AREF)
unnamed: C2.1, U2.13 (XTAL1), Y1.2
unnamed: C4.1, U2.12 (XTAL2), Y1.1
unnamed: R1.2, U2.9 (~RESET)
PA0: J2.4, J5.2, U1.2 (PA0), U2.40 (PA0)
PA1: J2.6, J5.15, U1.3 (PA1), U2.39 (PA1)
PA2: J2.8, J5.3, U1.4 (PA2), U2.38 (PA2)
PA3: J2.10, J5.16, U1.5 (PA3), U2.37 (PA3)
PA4: J2.9, J5.4, U1.6 (PA4), U2.36 (PA4)
PA5: J2.7, J5.17, U1.7 (PA5), U2.35 (PA5)
PA6: J2.5, J5.5, U1.8 (PA6), U2.34 (PA6)
PA7: J2.3, J5.18, U1.9 (PA7), U2.33 (PA7)
PB0: J1.4, J5.12, U1.10 (PB0), U2.1 (PB0)
PB1: J1.6, J5.24, U1.11 (PB1), U2.2 (PB1)
PB2: J1.8, J5.11, U1.12 (PB2), U2.3 (PB2)
PB3: J1.10, J5.23, U1.13 (PB3), U2.4 (PB3)
PB4: J1.9, J5.10, U1.14 (PB4), U2.5 (PB4)
PB5: J1.7, J5.22, U1.15 (PB5), U2.6 (PB5)
PB6: J1.5, J5.9, U1.16 (PB6), U2.7 (PB6)
PB7: J1.3, J5.21, U1.17 (PB7), U2.8 (PB7)
PHI2: J4.17, U1.25 (PHI2)
PS2CLK: J3.5, R2.1, U2.16 (PD2)
PS2DATA: J3.1, R3.1, U2.17 (PD3)
RESB: J4.3, U1.34 (RESB)
RWB: J4.13, U1.22 (RWB)
VCC: C1.2, C3.2, C6.1, C7.1, C8.2, J1.1, J2.1, J3.4, J4.2, J4.39, J5.1, J5.13, R1.1, R2.2, R3.2, U1.20 (VDD), U1.24 (CS1), U2.10 (VCC), U2.30 (AVCC), U3.16 (VCC)

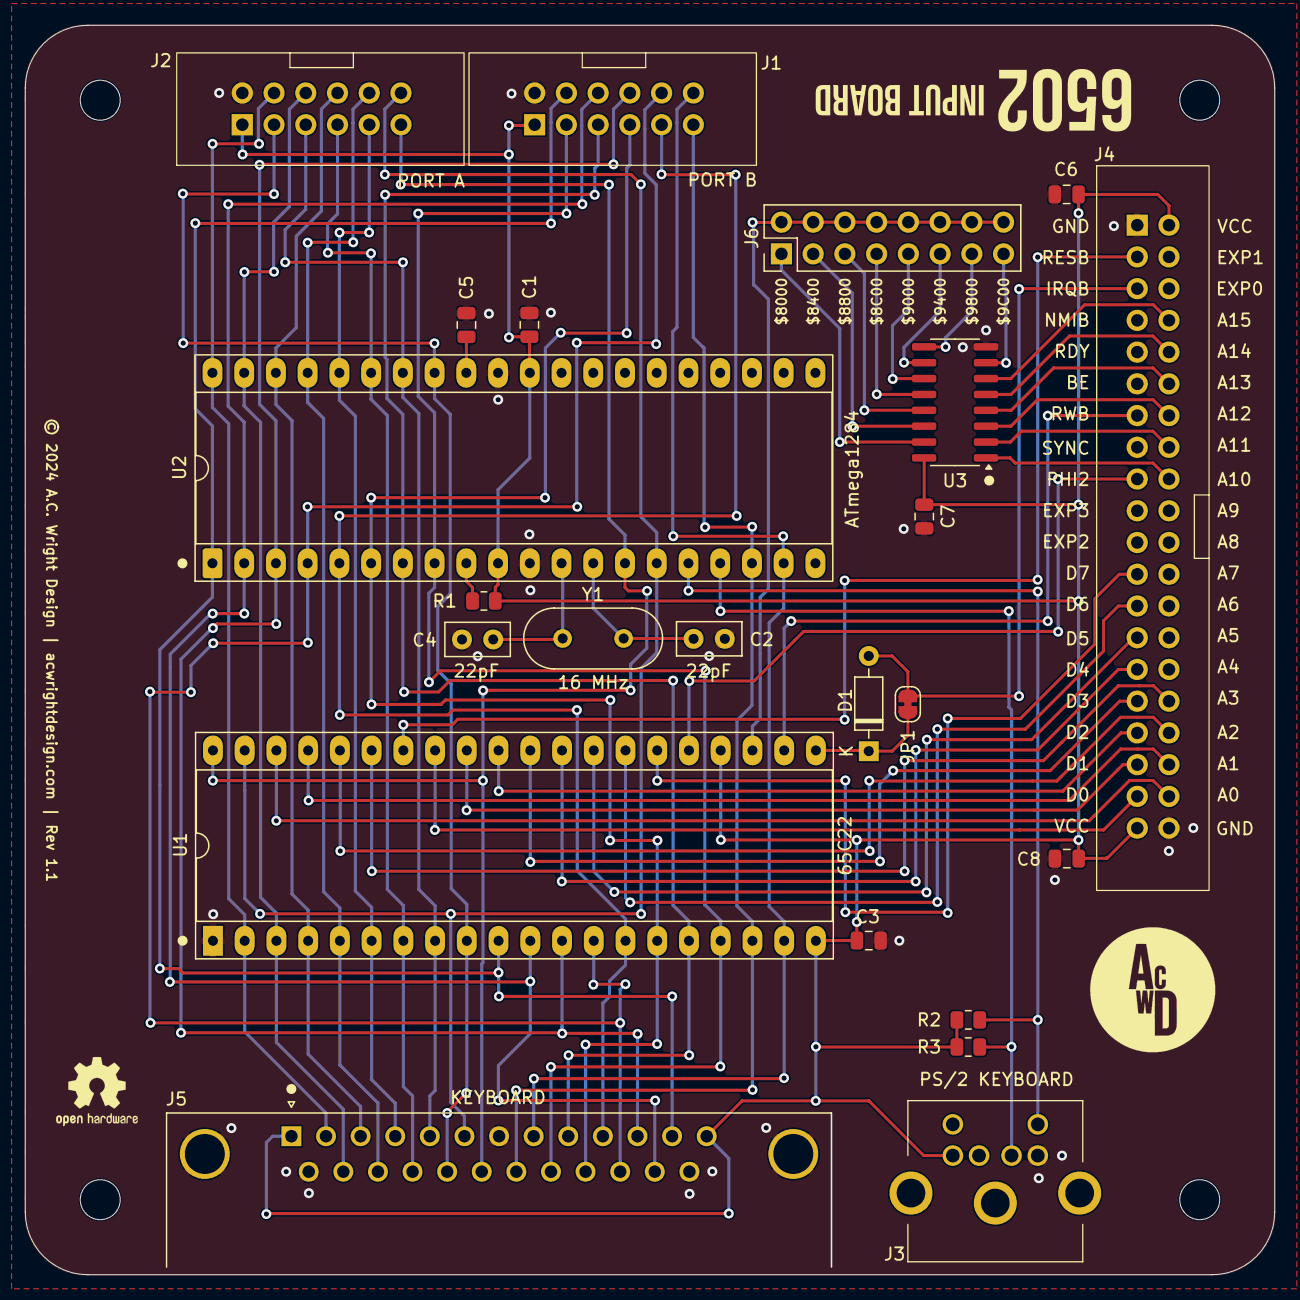
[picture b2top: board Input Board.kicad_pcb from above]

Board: 2 copper layers, 100.0 x 100.0 mm, 27 parts (0 on the bottom side), 60 nets.

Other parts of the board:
H1, H2, H3, H4: MountingHole; MountingHole_3.2mm_M3

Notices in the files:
README.md:
License:
Hardware designs are released under the [CERN Open Hardware Licence Version 2 – Permissive](https://ohwr.org/cern_ohl_p_v2.txt).
Firmware is released under the [MIT License](./Firmware/IB%20Controller/LICENSE).
Hardware/Flash Cart/Rev 1.0/Flash Cart.kicad_pcb:
© 2026 A.C. Wright Design | acwrightdesign.com | Rev 1.0
Hardware/Input Board/Rev 1.1/Input Board.kicad_pcb:
© 2024 A.C. Wright Design | acwrightdesign.com | Rev 1.1
Hardware/Output Board/Rev 1.0/Output Board.kicad_pcb:
© 2024 A.C. Wright Design | acwrightdesign.com | Rev 1.0
